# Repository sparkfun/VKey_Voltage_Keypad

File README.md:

**NOTE:** *This product has been retired from our catalog. If you are looking for more up-to-date info, please check out some of these resources to see how other users are still hacking and improving on this product.*

* *[SparkFun Forum](https://forum.sparkfun.com/)*
* *[Comments Here on GitHub](https://github.com/sparkfun/VKey_Voltage_Keypad/issues)*
* *[IRC Channel](https://www.sparkfun.com/news/263)*

VKey Voltage Keypad
===================

[*VKey Voltage Keypad(PRT_12080)*](https://www.sparkfun.com/products/12080)

12 Button keypad with analog voltage output.
Design and firmware files for the [VKey Voltage Keypad](https://www.sparkfun.com/products/12080).

Repository Contents
-------------------

* **/Documents** - Additional design files including LTspice simulation and parametric spreadsheets 
* **/Hardware** - Eagle PCB and schematic files
* **/Libraries** - Arduino library and example code
* **/Production** - Test bed files and production panel files

Documentation
--------------
* **[Library](https://github.com/sparkfun/SparkFun_VKey_Voltage_Keypad_Arduino_Library/tree/master)** - Arduino library for the VKey Voltage Keypad.
* **[Hookup Guide](https://learn.sparkfun.com/tutorials/vkey-voltage-keypad-hookup-guide)** - Basic hookup guide for the VKey Voltage Keypad.
* **[SparkFun 3D Model repo](https://github.com/sparkfun/3D_Models)** - 3D models of SparkFun products. 

License Information
-------------------
The hardware is released under [Creative Commons ShareAlike 4.0 International](https://creativecommons.org/licenses/by-sa/4.0/).
The code is beerware; if you see me (or any other SparkFun employee) at the local, and you've found our code helpful, please buy us a round!

Distributed as-is; no warranty is given.

Author: Byron Jacquot @ SparkFun Electonics

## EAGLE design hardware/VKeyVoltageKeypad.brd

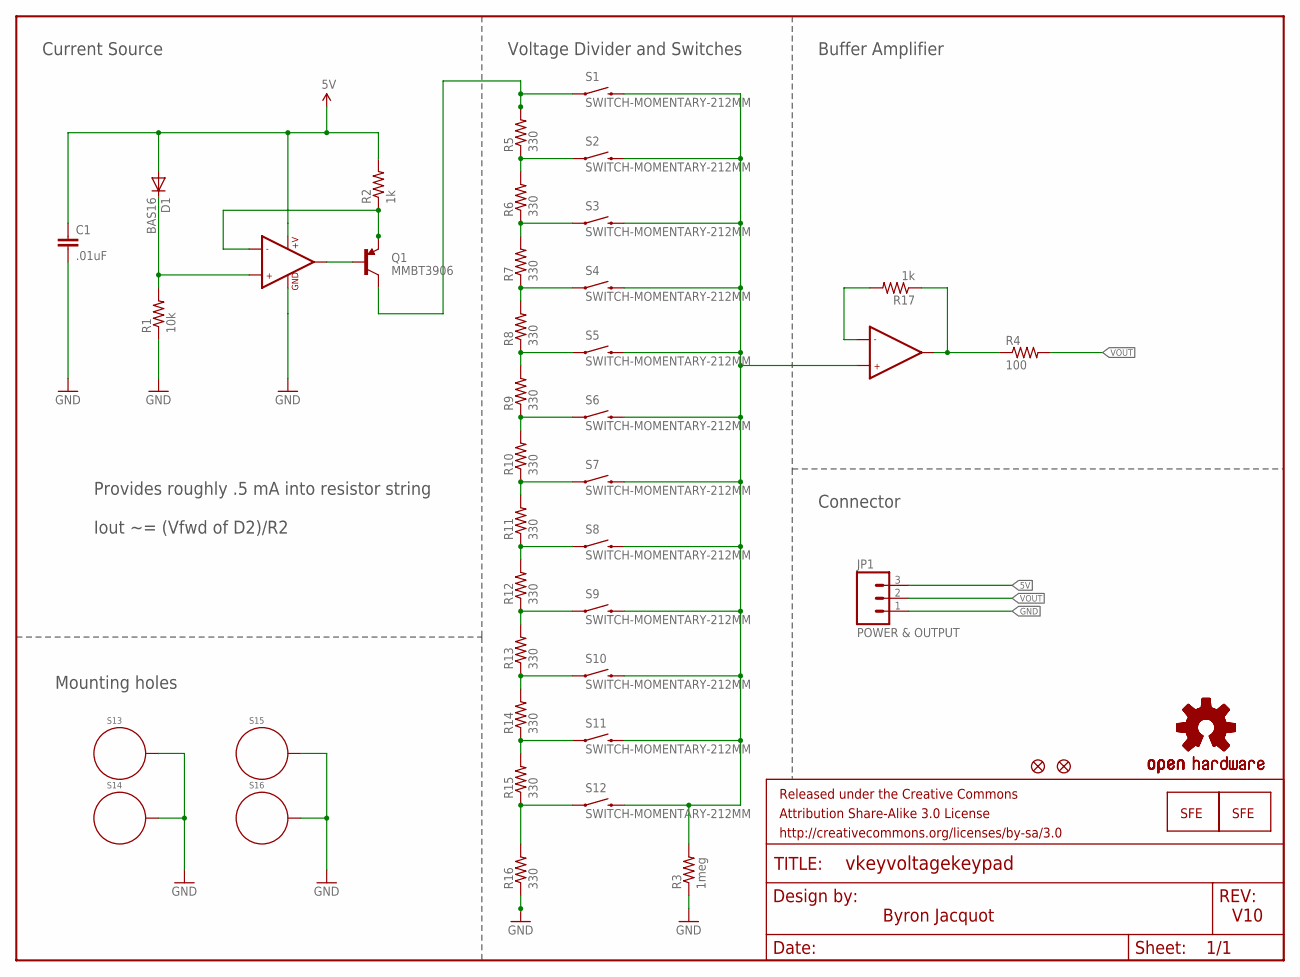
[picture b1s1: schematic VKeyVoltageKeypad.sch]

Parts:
C1: .01uF; 0603-CAP
D1: BAS16; SOD-323
FID1, FID2: FIDUCIALUFIDUCIAL; MICRO-FIDUCIAL
FRAME1: FRAME-LETTER; CREATIVE_COMMONS
JP1: POWER & OUTPUT; 1X03_NO_SILK
LOGO1, LOGO2: LOGO-SFENEW; SFE-NEW-WEBLOGO
LOGO3: OSHW-LOGOM; OSHW-LOGO-M
LOGO4: OSHW-LOGOL; OSHW-LOGO-L
Q1: MMBT3906; SOT23
R1: 10k; 0603-RES
R2, R17: 1k; 0603-RES
R3: 1meg; 0603-RES
R4: 100; 0603-RES
R5, R6, R7, R8, R9, R10, R11, R12, R13, R14, R15, R16: 330; 0603-RES
S1, S2, S3, S4, S5, S6, S7, S8, S9, S10, S11, S12: SWITCH-MOMENTARY-212MM; TACTILE-PTH-12MM
S13, S14, S15, S16: STANDOFF_ELECTRICAL; STANDOFF-ELECTRICAL
U1: LMV358; SO08

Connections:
5V: C1.1, D1.2 (A), JP1.3, R2.2, U1.8 (+V)
GND: C1.2, JP1.1, R1.1, R3.1, R16.1, S13.P1, S14.P1, S15.P1, S16.P1, U1.4 (GND)
unnamed: D1.1 (C), R1.2, U1.3 (+IN1)
unnamed: Q1.1 (B), U1.1 (OUT1)
unnamed: R3.2, S1.3 (2), S2.3 (2), S3.3 (2), S4.3 (2), S5.3 (2), S6.3 (2), S7.3 (2), S8.3 (2), S9.3 (2), S10.3 (2), S11.3 (2), S12.3 (2), U1.5 (+IN2)
unnamed: R14.1, R15.2, S11.1
unnamed: Q1.2 (E), R2.1, U1.2 (-IN1)
unnamed: Q1.3 (C), R5.2, S1.1
unnamed: R5.1, R6.2, S2.1
unnamed: R6.1, R7.2, S3.1
unnamed: R7.1, R8.2, S4.1
unnamed: R8.1, R9.2, S5.1
unnamed: R9.1, R10.2, S6.1
unnamed: R10.1, R11.2, S7.1
unnamed: R11.1, R12.2, S8.1
unnamed: R12.1, R13.2, S9.1
unnamed: R13.1, R14.2, S10.1
unnamed: R15.1, R16.2, S12.1
unnamed: R4.1, R17.1, U1.7 (OUT2)
unnamed: R17.2, U1.6 (-IN2)
VOUT: JP1.2, R4.2

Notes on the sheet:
V10
Current Source
Buffer Amplifier
Mounting holes
Voltage Divider and Switches
Connector
Provides roughly .5 mA into resistor string
Iout ~= (Vfwd of D2)/R2
Byron Jacquot

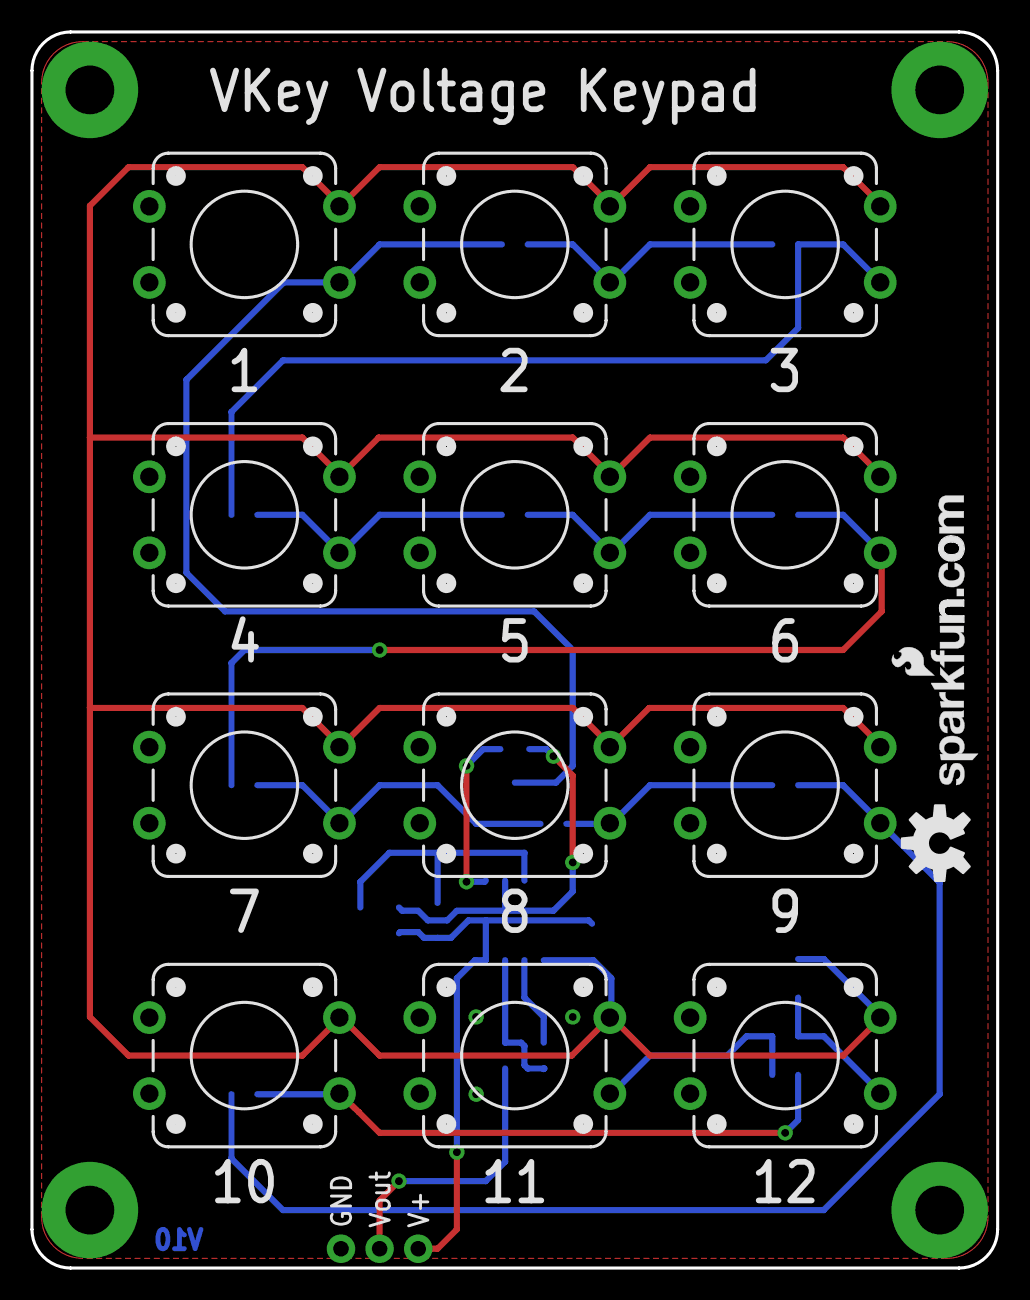
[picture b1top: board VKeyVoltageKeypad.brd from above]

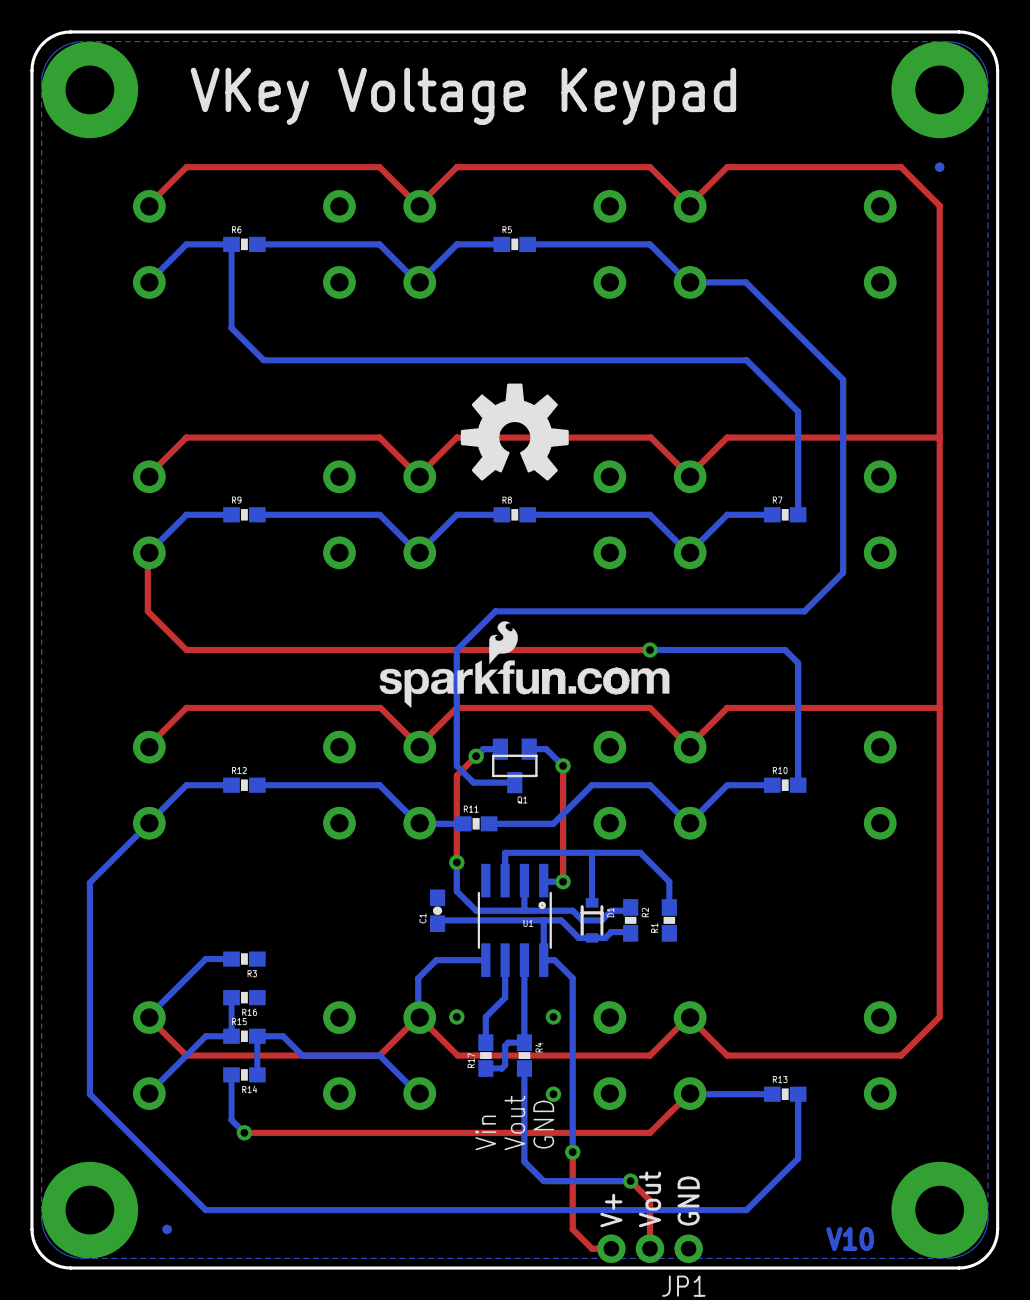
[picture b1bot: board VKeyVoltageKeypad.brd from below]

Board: 2 copper layers, 63.5 x 81.3 mm, 45 parts (26 on the bottom side), 21 nets.

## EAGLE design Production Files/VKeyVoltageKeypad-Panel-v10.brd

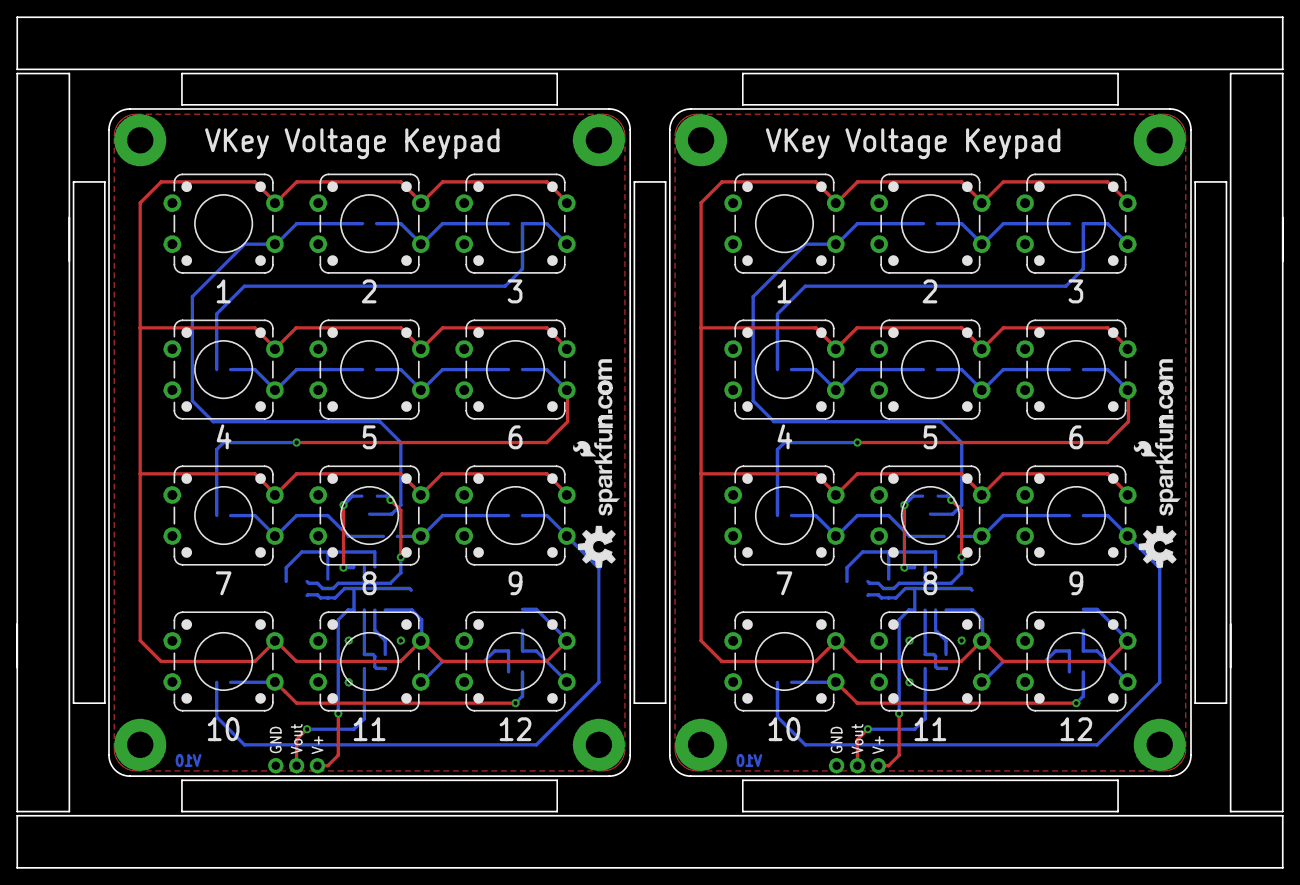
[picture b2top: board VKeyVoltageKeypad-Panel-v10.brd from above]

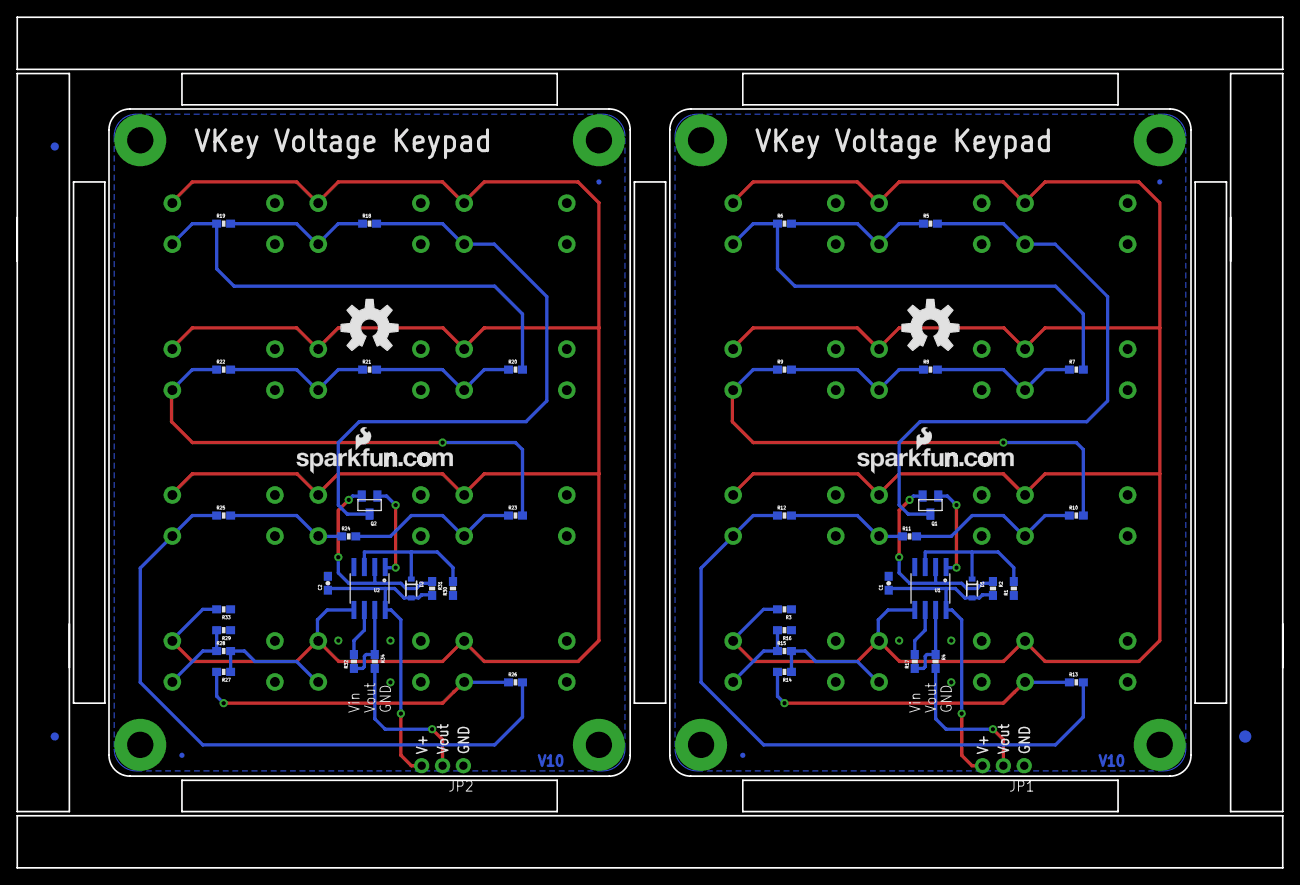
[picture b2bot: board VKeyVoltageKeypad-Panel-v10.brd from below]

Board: 2 copper layers, 154.2 x 103.6 mm, 91 parts (55 on the bottom side), 42 nets.

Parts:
C1, C2: .01uF; 0603-CAP
D1, D2: BAS16; SOD-323
E$1: FIDUCIAL-1.5X3
E$2, E$3: FIDUCIAL-1X2.5
FID1, FID2, FID3, FID4: FIDUCIALUFIDUCIAL; MICRO-FIDUCIAL
JP1, JP2: POWER & OUTPUT; 1X03_NO_SILK
LOGO1, LOGO2, LOGO5, LOGO6: LOGO-SFENEW; SFE-NEW-WEBLOGO
LOGO3, LOGO7: OSHW-LOGOM; OSHW-LOGO-M
LOGO4, LOGO8: OSHW-LOGOL; OSHW-LOGO-L
Q1, Q2: MMBT3906; SOT23
R1, R30: 10k; 0603-RES
R2, R17, R31, R32: 1k; 0603-RES
R3, R33: 1meg; 0603-RES
R4, R34: 100; 0603-RES
R5, R6, R7, R8, R9, R10, R11, R12, R13, R14, R15, R16, R18, R19, R20, R21, R22, R23, R24, R25, R26, R27, R28, R29: 330; 0603-RES
S1, S2, S3, S4, S5, S6, S7, S8, S9, S10, S11, S12, S17, S18, S19, S20, S21, S22, S23, S24, S25, S26, S27, S28: SWITCH-MOMENTARY-212MM; TACTILE-PTH-12MM
S13, S14, S15, S16, S29, S30, S31, S32: STANDOFF_ELECTRICAL; STANDOFF-ELECTRICAL
U1, U2: LMV358; SO08

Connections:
5V: C1.1, D1.2, JP1.3, R2.2, U1.8
5V1: C2.1, D2.2, JP2.3, R31.2, U2.8
GND: C1.2, JP1.1, R1.1, R3.1, R16.1, S13.P1, S14.P1, S15.P1, S16.P1, U1.4
GND1: C2.2, JP2.1, R29.1, R30.1, R33.1, S29.P1, S30.P1, S31.P1, S32.P1, U2.4
unnamed: D1.1, R1.2, U1.3
unnamed: Q1.1, U1.1
unnamed: R3.2, S1.3, S2.3, S3.3, S4.3, S5.3, S6.3, S7.3, S8.3, S9.3, S10.3, S11.3, S12.3, U1.5
unnamed: R14.1, R15.2, S11.1
unnamed: Q1.2, R2.1, U1.2
unnamed: Q1.3, R5.2, S1.1
unnamed: R5.1, R6.2, S2.1
unnamed: R6.1, R7.2, S3.1
unnamed: R7.1, R8.2, S4.1
unnamed: R8.1, R9.2, S5.1
unnamed: R9.1, R10.2, S6.1
unnamed: R10.1, R11.2, S7.1
unnamed: R11.1, R12.2, S8.1
unnamed: R12.1, R13.2, S9.1
unnamed: R13.1, R14.2, S10.1
unnamed: R15.1, R16.2, S12.1
unnamed: R4.1, R17.1, U1.7
unnamed: R17.2, U1.6
unnamed: D2.1, R30.2, U2.3
unnamed: Q2.2, R31.1, U2.2
unnamed: Q2.3, R18.2, S17.1
unnamed: R18.1, R19.2, S18.1
unnamed: R19.1, R20.2, S19.1
unnamed: R20.1, R21.2, S20.1
unnamed: R21.1, R22.2, S21.1
unnamed: R22.1, R23.2, S22.1
unnamed: R24.1, R25.2, S24.1
unnamed: R25.1, R26.2, S25.1
unnamed: R26.1, R27.2, S26.1
unnamed: R28.1, R29.2, S28.1
unnamed: R27.1, R28.2, S27.1
unnamed: Q2.1, U2.1
unnamed: R33.2, S17.3, S18.3, S19.3, S20.3, S21.3, S22.3, S23.3, S24.3, S25.3, S26.3, S27.3, S28.3, U2.5
unnamed: R23.1, R24.2, S23.1
unnamed: R32.1, R34.1, U2.7
unnamed: R32.2, U2.6
VOUT: JP1.2, R4.2
VOUT1: JP2.2, R34.2

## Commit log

2013-09-27 Initial commit of hardware and sim files
2013-10-17 Dressing up based on prototype review.
2013-10-21 Updates post review, moving to v10.
    Deleted C2,
    Moved connector to very edge of board.
    Put connector labels in tPlace.
2013-10-30 Added fiducials to board. Created Panel
2013-12-11 Starting on software
2014-01-23 Software and theory updates.
    A WIP checkin as I develop and test these.
2014-01-23 Chopping firmware into sketch & library.
2014-01-28 Updating firmware
    Many, many comments added.
2014-01-29 Cleanup towards going live
    Renamed "theory" folder to "documents."
    Added draft of hookup guide.
2014-01-30 More code cleanup
2014-01-30 Reorganizing software files.
2014-01-30 More organization of documentation.
    Deleting dead-end files, updating spreadsheets.
2014-02-03 Ready for review?
2014-02-04 Updated license & revised docs
2014-02-05 spelling fix
2014-02-07 Moved hookup materials into Sparkle.
2014-02-10 Integrating comments from code review.
2014-02-10 Updating README.md
2014-02-13 Updating README
2014-02-14 Adding Theory of Operation
2015-04-24 Squashed 'Libraries/Arduino/' content from commit bbd469c
    git-subtree-dir: Libraries/Arduino
    git-subtree-split: bbd469c850a7e0645b4705bdf5f013f2e8503aef
2015-04-24 Updating libraries/readme
2015-04-24 Renaming production directory
2015-04-29 Updating directories, README, file names
2015-04-29 Updating library update instructions
2015-04-29 Squashed 'Libraries/Arduino/' changes from bbd469c..6fbeb95
    git-subtree-dir: Libraries/Arduino
    git-subtree-split: 6fbeb959d90d6bb085e1aa565505af46928b8e10
2015-05-14 Squashed 'Libraries/Arduino/' changes from 6fbeb95..96bc1fa
    96bc1fa Updating version number in library.properties
    229e96f Fixing compilation errors
    git-subtree-dir: Libraries/Arduino
    git-subtree-split: 96bc1fa5e25971306459e8b7f5f8f017a0350c10

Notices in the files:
parts and their libraries:
SparkFun-Aesthetics: Licensing: CC v3.0 Share-Alike You are welcome to use this library for commercial purposes.
SparkFun-Aesthetics: Released under the Creative Commons Attribution Share-Alike 3.0 License
SparkFun-Aesthetics: http://creativecommons.org/licenses/by-sa/3.0
